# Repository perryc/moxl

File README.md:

# Mo-XL — Mower eXtra Large

An autonomous mower for large-scale grass areas like airstrips, built with ROS2 and RTK GPS.

## The Problem

Mowing a grass airstrip is a big job and the guy with the plane is often not around to cut it. This project has been kicking around for nearly 10 years now, but with "spring is coming soon" optimism, a lot of Claude Code help, and a few CDS2-ers pitching in — maybe we can cut some grass this year. The donor mower was chosen simply because we had one sitting at the farm not getting used.

The initial deployment is at CDS2 (Disley, Saskatchewan) — a 2246 ft x 78 ft grass runway that needs regular cutting. That's nearly half a mile of back-and-forth passes. RTK GPS gives centimeter-level accuracy in an open field. A robot can do this.

## The Approach

The [OpenMower](https://openmower.de/) project proved that a consumer mower can be converted to autonomous operation using ROS2, GPS, and off-the-shelf electronics. [OpenMowerNext](https://github.com/jkaflik/OpenMowerNext) by Jakub Kaflik rebuilt the software stack on modern ROS2 Jazzy with Nav2 and ros2_control.

Mo-XL takes that same architecture and scales it up — from a backyard lawn mower to a 60-inch commercial deck that can handle an airstrip. The software is forked from OpenMowerNext; the hardware is entirely custom.

## What Changed from OpenMowerNext

The fork keeps the proven ROS2 infrastructure — ros2_control, Nav2 path following, robot_localization EKF, Foxglove monitoring — and replaces everything hardware-specific:

| OpenMowerNext | Mo-XL | Why |
|---|---|---|
| VESC motor controllers | BTS7960 43A H-bridges | Different motors, 24V system |
| u-blox F9P GPS | FarmTRX RTK (CAN GPS) | We make this stuff! Let's use it |
| NTRIP client | Removed | FarmTRX handles its own RTK corrections |
| micro-ROS + custom mainboard | Mo-XL Pi HAT (custom PCB) | Single board, opto-isolated, JLCPCB assembled |
| IMU (on mainboard) | GPS magnetometer + gyro | FarmTRX sends heading (HDT/HCHDG) and rate of turn (TIROT) |
| Lawn polygon map server | Airstrip toolpath planner | Runway data from surveyed coordinates |
| Docking station | GPS park position | No charging dock — gas engine with alternator |
| YardForce 500B URDF | Custom URDF from measurements | Completely different machine |

## Hardware

### The Machine

A Swisher 60" towable rough-cut mower deck, converted from tow-behind to self-propelled:

- **Cutting deck**: Swisher 60" (1.52m), 3-blade triangle layout, B&S I/C 500cc 14.5 HP gas engine with electric start
- **Drive system**: Two electric wheelchair motors on 14.5" turf tires, chain-driven (19T→32T, 1.684:1), differential steering
- **Motor controllers**: 2x BTS7960 43A dual H-bridge boards, 24V PWM, 3.3V logic compatible
- **GPS**: FarmTRX RTK rover — NMEA0183 serial output, magnetometer heading (HDT/HCHDG), rate of turn gyro (TIROT), cm-level accuracy
- **I/O Board**: Mo-XL Pi HAT v1.0 — custom 6-layer PCB (see below)
- **Radio**: RTL-SDR v3/v4 USB dongle — monitors 122.8 MHz CTAF for aviation traffic
- **Computer**: Raspberry Pi 5 (8GB) running ROS2 Jazzy
- **Power**: 2x 12V lead-acid batteries in series (24V drive, 12V center tap for starter and Pi HAT)
- **Charging**: 24V alternator belt-driven off blade engagement belt — charges while mowing

### Key Dimensions

All dimensions from hangar measurements (Mar 2026) — see `config/hardware/moxl.yaml`.

| Measurement | Value |
|---|---|
| Rear wheel separation (center-to-center) | 1.321 m (52") |
| Rear wheel radius (turf tires) | 0.184 m (14.5" diameter) |
| Wheelbase (caster pivot to drive axle) | 1.105 m (43.5") |
| Caster separation | 1.016 m (40") |
| Cutting width | 1.52 m (60") |
| Chassis length | 1.137 m (44 3/4") |
| GPS antenna position | 0.127m fwd of drive axle, 0.80m AGL |
| Chain drive ratio | 19T motor → 32T wheel (1.684:1) |
| Total mass (estimated) | ~140 kg |

```
                 1.016m (40")
          ┌──────────────────────┐
    caster ○                      ○ caster
          │                      │
          │    1.105m wheelbase   │
          │                      │
          │      ★ GPS antenna   │
          │     (5" fwd of axle) │
          │                      │
    drive ●──────────────────────● drive
          └──────────────────────┘
                 1.321m (52")

    ●/○ = wheel    ★ = GPS antenna
    Front casters, rear drive (diff steer)
```

### Mo-XL Pi HAT v1.0

Custom Raspberry Pi 5 I/O board — single PCB replaces all direct GPIO wiring with isolated, protected I/O. 6-layer ENIG, 65 x 56.5mm Pi HAT form factor, assembled by JLCPCB.

Full spec sheet: [`hardware/moxl-hat/Mo-XL_Hat_v1.0_Spec.pdf`](hardware/moxl-hat/Mo-XL_Hat_v1.0_Spec.pdf)

| Feature | Implementation |
|---|---|
| **Power** | Hardened 12V input (TVS + EMI filter + polyfuse), XL4015 buck to 5.88V, TPS7A7001 LDO to 5.05V. Powers Pi and all HAT circuitry. |
| **2x Motor Drive** | 8 opto-isolated signals (TLP293-4) to BTS7960 modules via IDC ribbon cable. 20 kHz PWM. |
| **CAN / CAN-FD** | MCP251863T integrated controller + transceiver (SPI). TVS protected. |
| **RS-232** | MAX3221 on UART0. TX always active. |
| **SBUS** | RC receiver input via 74HC14 inverter on UART0 RX. Hardware-selectable vs RS-232 RX. |
| **4x Servo PWM** | PCA9685 16-ch PWM driver (I2C). 5.88V servo power rail. |
| **4x Analog Input** | ADS1115 16-bit ADC (I2C). On-board dividers for 12V/24V battery monitoring. |
| **K-type Thermocouple** | MAX31855 (SPI). Cylinder head temperature, 0-1024C. |
| **4x Relay Driver** | ULN2003A with flyback clamp. Engine run, start, blade engage, aux. |
| **4x Schmitt Trigger Input** | 74HC14 conditioned: engine tach + 2 wheel encoder pulses + SBUS. |
| **HAT ID EEPROM** | CAT24C256 on I2C0. Pi auto-configuration per HAT spec. |

KiCad source: [`hardware/moxl-hat/`](hardware/moxl-hat/)

### Connectors

| Connector | Type | Signals |
|---|---|---|
| J1 | JST-VH 2p | GND, +12V_RAW |
| J2 | JST-XH 4p | CANH, CANL, CAN_12V, GND |
| J3 | IDC 2x4 | Left motor (RPWM, LPWM, R_EN, L_EN, R_IS, L_IS, VCC, GND) |
| J4 | IDC 2x4 | Right motor (same as J3) |
| J5 | JST-XH 5p | RLY_RUN, RLY_START, RLY_BLADE, RLY_AUX, GND |
| J6 | JST-XH 8p | 4x servo PWM + 6V power + GND |
| J7 | JST-PH 5p | BATT_V, ALT_I, FUEL, PACK_V, GND |
| J8 | JST-PH 5p | RPM_SIG, ENC_L, ENC_R, 5V, GND |
| J9 | JST-XH 2p | TC+, TC- |
| J11 | JST-PH 3p | RS232_TX, RS232_RX, GND |
| J12 | JST-PH 3p | SBUS_IN, 5V, GND |

Unique pin counts per connector family prevent cross-plugging.

## Software Architecture

```
┌─────────────────────────────────────────────────────────────────┐
│                        moxl.launch.py                           │
├──────────┬──────────┬──────────┬──────────┬─────────────────────┤
│  URDF /  │   GPS    │  Local-  │  Nav2    │  Mission Control    │
│  ros2    │          │  ization │          │                     │
│  control │          │          │          │                     │
├──────────┼──────────┼──────────┼──────────┼─────────────────────┤
│ robot_   │ nmea_    │ heading  │ control  │ toolpath_node       │
│ state_   │ navsat_  │ _to_imu  │ _server  │ engine_controller   │
│ publisher│ driver   │ _node    │          │ blade_controller    │
│          │          │          │ planner  │ mission_node        │
│ controller         │ ekf_odom │ _server  │ safety_monitor      │
│ _manager │          │          │          │ sdr_detector        │
│          │ /gps/fix │ ekf_map  │ bt_nav   │                     │
│ diff_    │ /heading │          │          │                     │
│ drive_   │          │ navsat_  │ velocity │                     │
│ controller         │ transform│ _smoother│                     │
├──────────┴──────────┴──────────┴──────────┴─────────────────────┤
│                   twist_mux (with e-stop lock)                  │
├─────────────────────────────────────────────────────────────────┤
│                   Foxglove Bridge (web UI)                      │
└─────────────────────────────────────────────────────────────────┘
```

### ROS2 Nodes

**Localization** — GPS position and heading fused into odometry:
- `nmea_navsat_driver` — reads FarmTRX NMEA serial, publishes `/gps/fix` (NavSatFix), `/heading` (QuaternionStamped), and `/nmea_sentence` (raw NMEA for HCHDG/TIROT parsing)
- `heading_to_imu_node` — bridges GPS heading to `sensor_msgs/Imu` with speed-dependent covariance blending. Parses TIROT (rate of turn) for angular velocity and HCHDG as fallback heading source.
- `ekf_se_odom` — odom frame EKF: wheel odometry + magnetometer heading + gyro rate of turn
- `ekf_se_map` — map frame EKF: wheel odometry + GPS position + heading + gyro
- `navsat_transform_node` — converts GPS lat/lon to local map frame odometry

**Navigation** — Nav2 path following:
- `RegulatedPurePursuitController` — smooth path tracking tuned for large turning radius
- `SmacPlanner2D` — global path planning
- `VelocitySmoother` — acceleration limiting for smooth motion
- `twist_mux` — priority-based velocity command multiplexing (RC > navigation, e-stop locks all)

**Mission Control** — autonomous mowing orchestration:
- `toolpath_node` — generates headland-first mowing pattern: perimeter passes then parallel strips with step-in turns
- `engine_controller_node` — engine start/stop with CHT-driven choke logic (stub — HAT GPIO pending)
- `blade_controller_node` — blade engage/disengage via belt actuator relay (stub — HAT GPIO pending)
- `mission_node` — action server state machine: preflight (start engine, engage blades) → mow all strips via Nav2 FollowPath → return to park → shutdown. Monitors CTAF radio and evacuates when traffic is detected.
- `safety_monitor_node` — GPS fix watchdog (e-stop on RTK loss or timeout), future LiDAR obstacle detection
- `sdr_detector_node` — RTL-SDR radio traffic detector monitoring 122.8 MHz CTAF

### Custom ROS2 Interfaces

**Messages:**
- `EngineStatus.msg` — engine state (OFF/CRANKING/RUNNING/ERROR), RPM, cylinder head temp, choke
- `BladeStatus.msg` — blade state (DISENGAGED/ENGAGING/ENGAGED/DISENGAGING/ERROR)
- `MissionStatus.msg` — mission state, current strip, progress percentage
- `RadioDetection.msg` — SDR detection event: frequency, signal power, active flag, quiet duration

**Services:**
- `StartEngine.srv`, `StopEngine.srv` — engine control
- `SetBlades.srv` — blade engagement (engage/disengage)

**Actions:**
- `MowMission.action` — full autonomous mowing mission with feedback (strip progress, state)

### Toolpath Generation

The toolpath planner loads runway corner coordinates (RTK-surveyed at 0.02m accuracy), projects to UTM, and generates a headland-first mowing pattern:

1. Load runway polygon from `config/airstrips/CDS2.json`
2. Project WGS84 corners to UTM Zone 13N (EPSG:32613) via pyproj
3. Mow perimeter headland passes first (2 passes around the boundary)
4. Generate parallel strips for the interior with step-in turns
5. Densify each path with waypoints every 1.5m
6. All paths sent to Nav2 FollowPath (bypasses planner — open field needs no obstacle avoidance)

For CDS2 runway 11/29 (2246 ft x 78 ft) with a 60" deck and 5cm overlap: ~4.3 km total mowing distance.

### Aviation Radio Traffic Detector

You can't land if a mower is on the runway. Mo-XL monitors the airport traffic frequency with an RTL-SDR USB dongle (~$30) and automatically evacuates the runway when radio traffic is detected.

**How it works:**

1. `sdr_detector_node` tunes RTL-SDR to 122.8 MHz, reads IQ samples in a background thread, and computes signal power against a rolling noise floor
2. When a transmission is detected (power > noise floor + squelch threshold), the node publishes `radio_active=True` and asserts e-stop to immediately halt the mower
3. `mission_node` cancels the active FollowPath goal, navigates to the nearest pre-defined clear zone (off-runway safe area), and waits
4. After 5 minutes of radio silence, the mower resumes mowing from where it left off

**Clear zones** are defined per-runway in `CDS2.json` — three safe parking areas (north apron, midfield west, south holdshort) where the mower can wait without blocking the runway.

**Fail-open design:** If the RTL-SDR hardware isn't connected or `pyrtlsdr` isn't installed, the detector logs a warning and publishes `radio_active=False` — mowing continues unblocked. The GPS safety monitor remains the hard backstop.

## Target Airstrip

**CDS2** — Disley, Saskatchewan, Canada

| | |
|---|---|
| Runway | 11/29 |
| Dimensions | 2246 ft x 78 ft (685 m x 24 m) |
| Heading | ~117° true |
| Elevation | 1847–1861 ft |
| Magnetic declination | 7.2° East |
| UTM Zone | 13N (EPSG:32613) |

All four runway corners RTK-surveyed at 0.02m accuracy:

| Corner | Latitude | Longitude |
|---|---|---|
| NW | 50.63612190 | -105.03202723 |
| NE | 50.63603243 | -105.03175091 |
| SE | 50.63285006 | -105.03165067 |
| SW | 50.63288086 | -105.03194065 |

## Project Structure

```
moxl/
├── config/
│   ├── airstrips/CDS2.json          # RTK-surveyed runway corners
│   ├── controllers.yaml             # ros2_control diff_drive params
│   ├── gps.yaml                     # nmea_navsat_driver config
│   ├── hardware/moxl.yaml           # Physical dimensions (from hangar measurements)
│   ├── mowing_params.yaml           # Cutting width, overlap, speed
│   ├── nav2_params.yaml             # Nav2 path following tuning
│   ├── robot_localization.yaml      # Dual EKF + navsat_transform
│   └── twist_mux.yaml              # Velocity priority + e-stop lock
├── description/                     # URDF/xacro robot model
│   ├── robot.urdf.xacro            # Top-level URDF
│   ├── robot_core.xacro            # Chassis, wheels, casters, deck
│   ├── gps.xacro                   # GPS antenna link + visual
│   └── ros2_control.xacro          # BTS7960 hw_interface (mock on desktop)
├── docs/
│   ├── moxl-hat-spec.md            # Pi HAT full specification
│   └── wiring/moxl_harness.yml     # WireViz wiring harness diagram
├── hardware/moxl-hat/              # KiCad PCB design
│   ├── moxl-hat.kicad_sch          # Schematic (clean DRC)
│   ├── moxl-hat.kicad_pcb          # 6-layer PCB layout
│   ├── Mo-XL_Hat_v1.0_Spec.pdf     # Spec sheet with schematic
│   ├── pinout-table.dxf            # Bottom silk pinout (for KiCad import)
│   └── production/                 # JLCPCB fabrication files (BOM, positions, Gerbers)
├── launch/
│   ├── moxl.launch.py              # Full system launch
│   ├── gps.launch.py               # GPS driver
│   ├── localization.launch.py      # EKF + navsat_transform + heading bridge
│   ├── nav2.launch.py              # Navigation stack
│   ├── mission.launch.py           # Mission control nodes
│   ├── joystick.launch.py          # Manual teleop
│   └── sim.launch.py               # Gazebo simulation
├── src/
│   ├── msg/                         # EngineStatus, BladeStatus, MissionStatus, RadioDetection
│   ├── srv/                         # StartEngine, StopEngine, SetBlades
│   ├── action/                      # MowMission
│   ├── toolpath_planner/            # Python ROS2 package
│   │   ├── toolpath_planner/        # Core library
│   │   │   ├── coordinate_utils.py  # WGS84 ↔ UTM conversion
│   │   │   ├── polygon_loader.py    # Airport JSON → runway corners
│   │   │   └── strip_generator.py   # Headland-first pattern generation
│   │   ├── nodes/                   # ROS2 nodes
│   │   │   ├── toolpath_node.py
│   │   │   ├── heading_to_imu_node.py
│   │   │   ├── engine_controller_node.py
│   │   │   ├── blade_controller_node.py
│   │   │   ├── mission_node.py
│   │   │   ├── safety_monitor_node.py
│   │   │   └── sdr_detector_node.py
│   │   └── test/                    # 31 unit tests
│   └── lib/bts7960_hw_interface/    # C++ ros2_control plugin (TBD)
├── photos/                          # Build photos & measurements
├── HARDWARE_TODO.md                 # Hardware integration checklist
└── worlds/                          # Gazebo simulation worlds
```

## Getting Started

### Prerequisites

ROS2 Jazzy on Ubuntu 24.04 (or Raspberry Pi OS with ROS2):

```bash
sudo apt install \
  ros-jazzy-ros2-control ros-jazzy-ros2-controllers \
  ros-jazzy-diff-drive-controller ros-jazzy-robot-localization \
  ros-jazzy-nmea-navsat-driver ros-jazzy-navigation2 \
  ros-jazzy-teleop-twist-keyboard ros-jazzy-foxglove-bridge \
  ros-jazzy-xacro ros-jazzy-robot-state-publisher \
  ros-jazzy-twist-mux
```

Python dependencies:

```bash
pip install pyproj shapely numpy
```

### Build

```bash
cd ~/ros2_ws/src
git clone https://github.com/perryc/moxl.git
cd ~/ros2_ws
colcon build
source install/setup.bash
```

### Run Tests

```bash
cd src/moxl/src/toolpath_planner
python3 -m pytest test/ -v
```

All 31 tests cover coordinate conversion accuracy, strip generation geometry, and polygon loading.

### Simulation

Runs Gazebo simulation with full Nav2 navigation, toolpath planning, and mission control.

```bash
source /opt/ros/jazzy/setup.bash
cd ~/moxl && colcon build && source install/setup.bash
ros2 launch moxl sim.launch.py

# Send a mowing mission (in a second terminal)
ros2 action send_goal /moxl/mission moxl/action/MowMission \
  '{airstrip_id: CDS2, runway_id: "11/29"}' --feedback
```

> **Important:** Gazebo loads the world file from `install/`, not from `worlds/` in the source tree.
> After any change to `worlds/empty.sdf` (or a `git pull` that updates it), you must
> `colcon build` again so the updated file is copied into the install directory.

### Launch (Native ROS2)

```bash
# Full system (uses mock hardware interface on desktop)
ros2 launch moxl moxl.launch.py

# Manual teleop for testing
ros2 launch moxl joystick.launch.py
```

### Start a Mowing Mission

```bash
ros2 action send_goal /moxl/mission moxl/action/MowMission \
  "{airstrip_id: 'CDS2', runway_id: '11/29'}"
```

The mission sequences through: preflight (engine start, blade engage) → mow all strips → return to park → shutdown. Monitor progress via Foxglove at `ws://localhost:8765`.

## Status

This is an active build. The software architecture is complete; hardware integration is in progress. Pi HAT boards ordered from JLCPCB.

- [x] Fork and adapt OpenMowerNext
- [x] BTS7960 hardware interface (ros2_control plugin defined, mock for desktop)
- [x] URDF robot description (from hangar measurements, all dimensions verified)
- [x] GPS integration (nmea_navsat_driver + magnetometer heading + TIROT gyro bridge)
- [x] Toolpath planner (headland-first pattern, 31 tests passing)
- [x] Mission control (action server state machine, engine/blade stubs)
- [x] Safety monitor (GPS watchdog + e-stop)
- [x] Mo-XL Pi HAT v1.0 designed (KiCad, 6-layer, clean DRC, JLCPCB production files)
- [x] Wiring harness diagram (WireViz)
- [x] Gazebo simulation — full autonomous mowing mission completes
- [x] Aviation radio traffic detector — RTL-SDR monitors 122.8 MHz CTAF, auto-evacuates runway
- [ ] Pi HAT assembly and smoke test (boards ordered, 10 days out)
- [ ] BTS7960 GPIO driver (compile for Pi, wire motors via HAT J3/J4)
- [ ] Engine control via HAT (starter relay, choke servo, RPM tach, CHT thermocouple)
- [ ] Blade engagement via HAT (relay + belt actuator)
- [ ] Belt-driven alternator for 24V charging
- [ ] Wheel encoder pulse counters (via HAT 74HC14 inputs)
- [ ] LiDAR obstacle detection (RPLIDAR C1 ordered)
- [ ] RC manual override (SBUS via HAT)
- [ ] Field testing at CDS2

See [HARDWARE_TODO.md](HARDWARE_TODO.md) for the full hardware integration checklist.

## Acknowledgments

- [OpenMowerNext](https://github.com/jkaflik/OpenMowerNext) by Jakub Kaflik — the ROS2 foundation this project is built on
- [OpenMower](https://openmower.de/) by Clemens Elflein — the original open-source autonomous mower that proved the concept
- [Nav2](https://nav2.org/) — battle-tested robot navigation
- [robot_localization](https://docs.ros.org/en/jazzy/p/robot_localization/) — GPS + odometry fusion
- [WireViz](https://github.com/wireviz/WireViz) — wiring harness documentation
- Jack C — bled for the initial measurements so we didn't have to

## License

Apache 2.0 — see [LICENSE](LICENSE). Original OpenMowerNext code is also Apache 2.0.

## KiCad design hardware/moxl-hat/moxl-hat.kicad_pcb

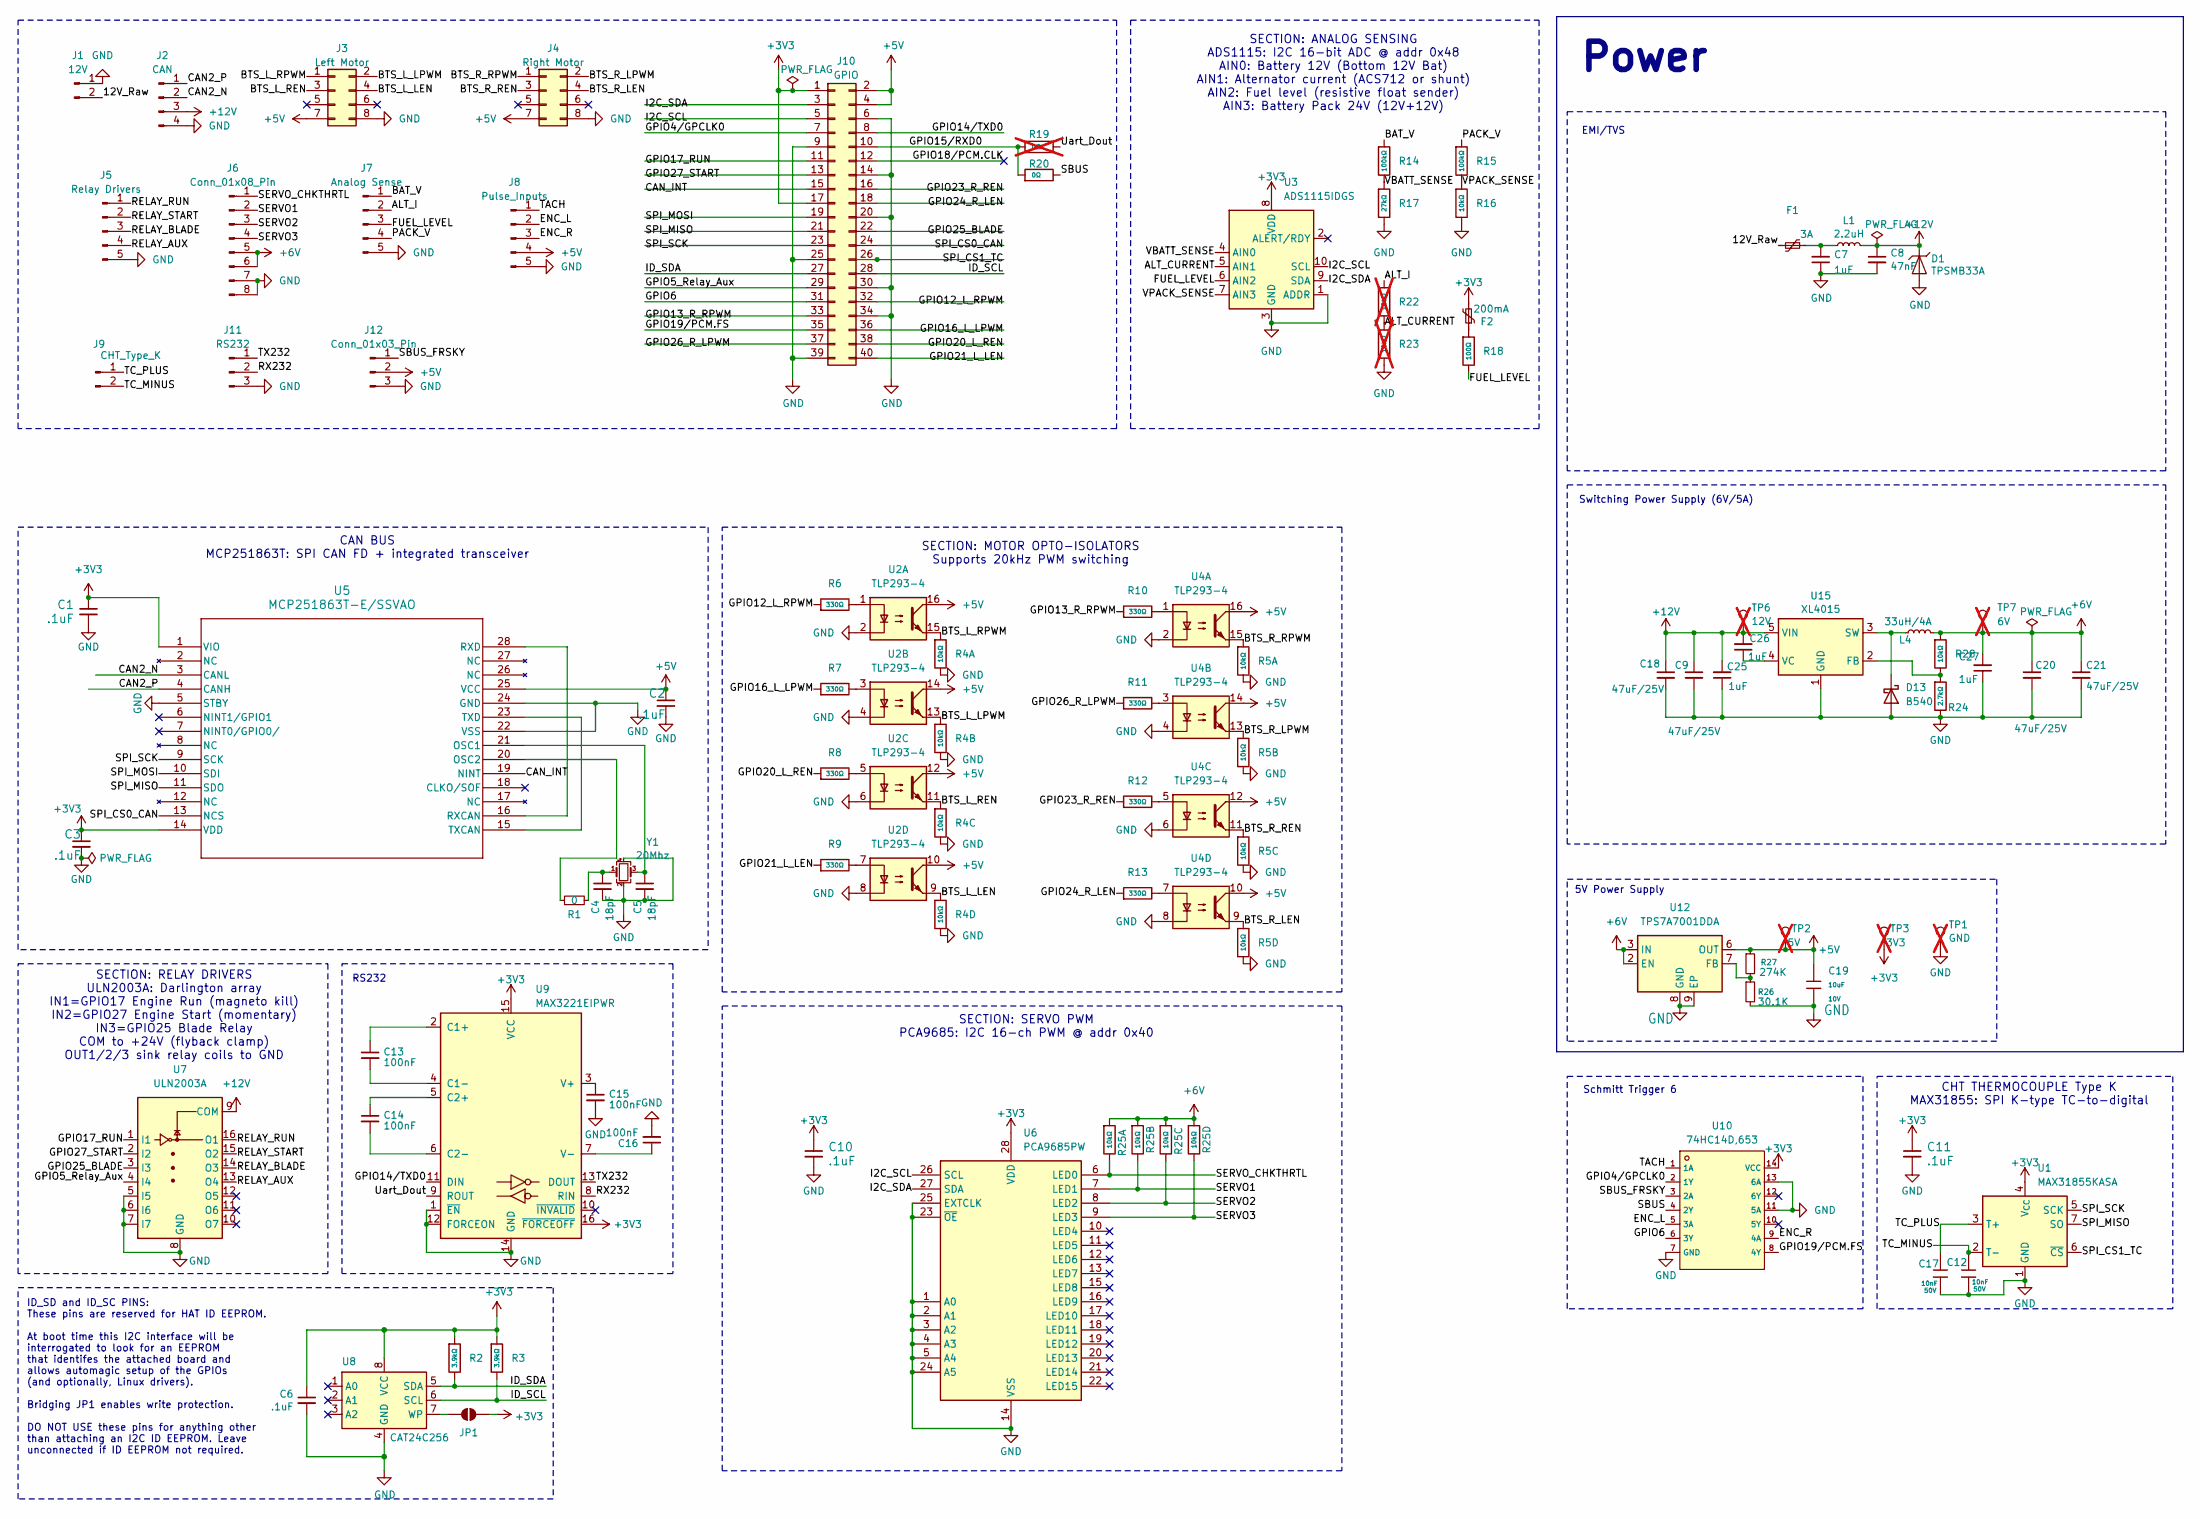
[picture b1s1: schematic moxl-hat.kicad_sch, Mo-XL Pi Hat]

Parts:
C1, C2, C3, C10, C11: .1uF; C_0603_1608Metric; Part Number CL10B104KC8NNNC; LCSC C14663
C4, C5: 18pF; C_0402_1005Metric; LCSC C1549
C6: .1uF; C_0603_1608Metric; LCSC C14663
C7, C25, C26, C27: 1uF; C_0805_2012Metric; LCSC C28323
C8: 47nF; C_0805_2012Metric; Part Number CL21B473KBCNNNC; LCSC C53134
C9, C18, C20, C21: 47uF/25V; C_1210_3225Metric; LCSC C90142
C12, C17: 10nF; C_0402; Voltage Rated 50V; Tolerance ±10%; Part CL05B103KB5NNNC; LCSC C15195
C13, C14, C15, C16: 100nF; C_0402_1005Metric; LCSC C307331
C19: 10uF; C_0603; Voltage Rated 10V; Tolerance ±10%; Part CL10A106KP8NNNC; LCSC C19702
D1: TPSMB33A; D_SMB; LCSC C726834
D13: B540; D_SMC; LCSC C72264
F1: 3A; Fuse_1812_4532Metric; LCSC C20627123
F2: 200mA; Fuse_0805_2012Metric; LCSC C20976
J1: 12V; JST_VH_B2P-VH-B_1x02_P3.96mm_Vertical; LCSC C495202
J2: CAN; JST_XH_B4B-XH-A_1x04_P2.50mm_Vertical; LCSC C594232
J3: Left Motor; PinHeader_2x04_P2.54mm_Vertical
J4: Right Motor; PinHeader_2x04_P2.54mm_Vertical
J5: Relay Drivers; JST_XH_B5B-XH-A_1x05_P2.50mm_Vertical; LCSC C157991
J6: Conn_01x08_Pin; JST_XH_B8B-XH-A_1x08_P2.50mm_Vertical; LCSC C157972
J7: Analog Sense; JST_PH_B5B-PH-K_1x05_P2.00mm_Vertical; LCSC C157993
J8: Pulse_Inputs; JST_PH_B5B-PH-K_1x05_P2.00mm_Vertical; LCSC C157993
J9: CHT_Type_K; JST_XH_B2B-XH-A_1x02_P2.50mm_Vertical; LCSC C158012
J10: GPIO; PinSocket_2x20_P2.54mm_Vertical
J11: RS232; JST_PH_B3B-PH-K_1x03_P2.00mm_Vertical; LCSC C131339
J12: Conn_01x03_Pin; JST_PH_B3B-PH-K_1x03_P2.00mm_Vertical; LCSC C131339
JP1: ID_WP; SolderJumper-2_P1.3mm_Bridged_RoundedPad1.0x1.5mm
L1: 2.2uH; L_6.3x6.3_H3; Part Number TMPC0618H-2R2MG-D; LCSC C305216
L4: 33uH/4A; L_Changjiang_FXL1040; LCSC C436575
R1: 0; R_0402_1005Metric; LCSC C17168
R2, R3: 3.9kΩ; R_0402; Overload Voltage (Max) 50V; Tolerance ±1%; Part 0402WGF3901TCE; LCSC C51721
R4, R5, R25: 10kΩ; R_0603x4; Tolerance ±5%; Part 4D03WGJ0103T5E; LCSC C29718
R6, R7, R8, R9, R10, R11, R12, R13: 330Ω; R_0603; Overload Voltage (Max) 75V; Tolerance ±1%; Part 0603WAF3300T5E; LCSC C23138
R14, R15: 100kΩ; R_0603; Overload Voltage (Max) 75V; Tolerance ±1%; Part 0603WAF1003T5E; LCSC C25803
R16, R28: 10kΩ; R_0603; Overload Voltage (Max) 75V; Tolerance ±1%; Part 0603WAF1002T5E; LCSC C25804
R17: 27kΩ; R_0603; Overload Voltage (Max) 75V; Tolerance ±1%; Part 0603WAF2702T5E; LCSC C22967
R18: 100Ω; R_0603; Overload Voltage (Max) 75V; Tolerance ±1%; Part 0603WAF1000T5E; LCSC C22775
R19: 0Ω; R_0603; Overload Voltage (Max) 75V; Tolerance ±1%; Part 0603WAF0000T5E; LCSC C21189; not fitted
R20: 0Ω; R_0603; Overload Voltage (Max) 75V; Tolerance ±1%; Part 0603WAF0000T5E; LCSC C21189
R22, R23: 10kΩ; R_0603; Overload Voltage (Max) 75V; Tolerance ±1%; Part 0603WAF1002T5E; LCSC C25804; not fitted
R24: 2.7kΩ; R_0603; Overload Voltage (Max) 75V; Tolerance ±1%; Part 0603WAF2701T5E; LCSC C13167
R26: 30.1K; R_0603; LCSC C23000
R27: 274K; R_0603; LCSC C22968
TP1: GND; TestPoint_THTPad_D1.5mm_Drill0.7mm; not fitted
TP2: 5V; TestPoint_THTPad_D1.5mm_Drill0.7mm; not fitted
TP3: 3V3; TestPoint_THTPad_D1.5mm_Drill0.7mm; not fitted
TP6: 12V; TestPoint_THTPad_D1.5mm_Drill0.7mm; not fitted
TP7: 6V; TestPoint_THTPad_D1.5mm_Drill0.7mm; not fitted
U1: MAX31855KASA; SOIC-8_3.9x4.9mm_P1.27mm; LCSC C52028
U2, U4: TLP293-4; SOIC-16_4.55x10.3mm_P1.27mm; LCSC C112623
U3: ADS1115IDGS; TSSOP-10_3x3mm_P0.5mm; LCSC C2868291
U5: MCP251863T-E/SSVAO; SSOP-28_5.3x10.2mm_P0.65mm; LCSC C5226885
U6: PCA9685PW; TSSOP-28_4.4x9.7mm_P0.65mm; LCSC C2678753
U7: ULN2003A; SOP-16_4.4x10.4mm_P1.27mm; LCSC C482013
U8: CAT24C256; TSSOP-8_4.4x3mm_P0.65mm; LCSC C79987
U9: MAX3221EIPWR; TSSOP-16_4.4x5mm_P0.65mm; LCSC C484736
U10: 74HC14D,653; SOIC-14_L8.7-W3.9-P1.27-LS6.0-BL; Supply Voltage(Single) 2V~6V; Part 74HC14D,653; LCSC C5605
U12: TPS7A7001DDA; TI_SO-PowerPAD-8; LCSC C60719
U15: XL4015; TO-263-5_TabPin3; LCSC C51661
Y1: 20Mhz; Crystal_SMD_5032-4Pin_5.0x3.2mm; Part Number TAXM20M4QLDCDT2T; LCSC C362490

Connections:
+3V3: C1.1, C3.1, C6.1, C10.1, C11.1, F2.2, J10.1, J10.17, JP1.2 (B), R2.1, R3.1, TP3.1, U1.4 (V_{CC}), U3.8 (VDD), U5.1 (VIO), U5.14 (VDD), U6.28 (VDD), U8.8 (VCC), U9.15 (VCC), U9.16 (~FORCEOFF), U10.14 (VCC)
+5V: C2.1, C19.1, J3.7, J4.7, J8.4, J10.2, J10.4, J12.2, R27.1, TP2.1, U2.10, U2.12, U2.14, U2.16, U4.10, U4.12, U4.14, U4.16, U5.25 (VCC), U12.6 (OUT)
+6V: C20.1, C21.1, C27.2, J6.5, J6.6, L4.2, R25.1, R25.2, R25.3, R25.4, R28.1, TP7.1, U12.2 (EN), U12.3 (IN)
+12V: C8.1, C9.1, C18.1, C25.2, C26.2, D1.1 (A1), J2.3, L1.2, TP6.1, U7.9 (COM), U15.5 (VIN)
/12V_Raw: F1.2, J1.2
/ALT_CURRENT: R22.2, R23.1, U3.5 (AIN1)
/ALT_I: J7.2, R22.1
/BAT_V: J7.1, R14.1
/BTS_L_LEN: J3.4, R4.4, U2.9
/BTS_L_LPWM: J3.2, R4.2, U2.13
/BTS_L_REN: J3.3, R4.3, U2.11
/BTS_L_RPWM: J3.1, R4.1, U2.15
/BTS_R_LEN: J4.4, R5.4, U4.9
/BTS_R_LPWM: J4.2, R5.2, U4.13
/BTS_R_REN: J4.3, R5.3, U4.11
/BTS_R_RPWM: J4.1, R5.1, U4.15
/CAN2_N: J2.2, U5.3 (CANL)
/CAN2_P: J2.1, U5.4 (CANH)
/CAN_INT: J10.15, U5.19 (NINT)
/ENC_L: J8.2, U10.5 (3A)
/ENC_R: J8.3, U10.9 (4A)
/FUEL_LEVEL: J7.3, R18.2, U3.6 (AIN2)
/GPIO4/GPCLK0: J10.7, U10.2 (1Y)
/GPIO5_Relay_Aux: J10.29, U7.4 (I4)
/GPIO6: J10.31, U10.6 (3Y)
/GPIO12_L_RPWM: J10.32, R6.1
/GPIO13_R_RPWM: J10.33, R10.1
/GPIO14/TXD0: J10.8, U9.11 (DIN)
/GPIO15/RXD0: J10.10, R19.1, R20.1
/GPIO16_L_LPWM: J10.36, R7.1
/GPIO17_RUN: J10.11, U7.1 (I1)
/GPIO18/PCM.CLK: J10.12
/GPIO19/PCM.FS: J10.35, U10.8 (4Y)
/GPIO20_L_REN: J10.38, R8.1
/GPIO21_L_LEN: J10.40, R9.1
/GPIO23_R_REN: J10.16, R12.1
/GPIO24_R_LEN: J10.18, R13.1
/GPIO25_BLADE: J10.22, U7.3 (I3)
/GPIO26_R_LPWM: J10.37, R11.1
/GPIO27_START: J10.13, U7.2 (I2)
/I2C_SCL: J10.5, U3.10 (SCL), U6.26 (SCL)
/I2C_SDA: J10.3, U3.9 (SDA), U6.27 (SDA)
/ID_SCL: J10.28, R3.2, U8.6 (SCL)
/ID_SDA: J10.27, R2.2, U8.5 (SDA)
/PACK_V: J7.4, R15.1
/RELAY_AUX: J5.4, U7.13 (O4)
/RELAY_BLADE: J5.3, U7.14 (O3)
/RELAY_RUN: J5.1, U7.16 (O1)
/RELAY_START: J5.2, U7.15 (O2)
/RX232: J11.2, U9.8 (RIN)
/SBUS: R20.2, U10.4 (2Y)
/SBUS_FRSKY: J12.1, U10.3 (2A)
/SERVO1: J6.2, R25.7, U6.7 (LED1)
/SERVO2: J6.3, R25.6, U6.8 (LED2)
/SERVO3: J6.4, R25.5, U6.9 (LED3)
/SERVO_CHKTHRTL: J6.1, R25.8, U6.6 (LED0)
/SPI_CS0_CAN: J10.24, U5.13 (NCS)
/SPI_CS1_TC: J10.26, U1.6 (~CS)
/SPI_MISO: J10.21, U1.7 (SO), U5.11 (SDO)
/SPI_MOSI: J10.19, U5.10 (SDI)
/SPI_SCK: J10.23, U1.5 (SCK), U5.9 (SCK)
/TACH: J8.1, U10.1 (1A)
/TC_MINUS: C12.1, J9.2, U1.2 (T-)
/TC_PLUS: C17.1, J9.1, U1.3 (T+)
/TX232: J11.1, U9.13 (DOUT)
/Uart_Dout: R19.2, U9.9 (ROUT)
/VBATT_SENSE: R14.2, R17.1, U3.4 (AIN0)
/VPACK_SENSE: R15.2, R16.1, U3.7 (AIN3)
GND: C1.2, C2.2, C3.2, C4.2, C5.2, C6.2, C7.1, C8.2, C9.2, C10.2, C11.2, C12.2, C15.2, C16.2, C17.2, C18.2, C19.2, C20.2, C21.2, C25.1, C27.1, D1.2 (A2), D13.2 (A), J1.1, J2.4, J3.8, J4.8, J5.5, J6.7, J6.8, J7.5, J8.5, J10.6, J10.9, J10.14, J10.20, J10.25, J10.30, J10.34, J10.39, J11.3, J12.3, R4.5, R4.6, R4.7, R4.8, R5.5, R5.6, R5.7, R5.8, R16.2, R17.2, R23.2, R24.2, R26.2, TP1.1, U1.1 (GND), U2.2, U2.4, U2.6, U2.8, U3.1 (ADDR), U3.3 (GND), U4.2, U4.4, U4.6, U4.8, U5.5 (STBY), U5.22 (VSS), U5.24 (GND), U6.1 (A0), U6.2 (A1), U6.3 (A2), U6.4 (A3), U6.5 (A4), U6.14 (VSS), U6.23 (~OE), U6.24 (A5), U6.25 (EXTCLK), U7.5 (I5), U7.6 (I6), U7.7 (I7), U7.8 (GND), U8.4 (GND), U9.1 (~EN), U9.12 (FORCEON), U9.14 (GND), U10.7 (GND), U10.11 (5A), U10.13 (6A), U12.8 (GND), U12.9 (EP), U15.1 (GND), Y1.2, Y1.4
unnamed: C4.1, R1.2, Y1.1
unnamed: C7.2, F1.1, L1.1
unnamed: D13.1 (K), L4.1, U15.3 (SW)
unnamed: F2.1, R18.1
unnamed: JP1.1 (A), U8.7 (WP)
unnamed: R6.2, U2.1
unnamed: R7.2, U2.3
unnamed: R8.2, U2.5
unnamed: R9.2, U2.7
unnamed: R10.2, U4.1
unnamed: R11.2, U4.3
unnamed: R12.2, U4.5
unnamed: R13.2, U4.7
unnamed: C5.1, U5.21 (OSC1), Y1.3
unnamed: R1.1, U5.20 (OSC2)
unnamed: U5.16 (RXCAN), U5.28 (RXD)
unnamed: U5.15 (TXCAN), U5.23 (TXD)
unnamed: C13.1, U9.2 (C1+)
unnamed: C13.2, U9.4 (C1-)
unnamed: C14.1, U9.5 (C2+)
unnamed: C14.2, U9.6 (C2-)
unnamed: C15.1, U9.3 (V+)
unnamed: C16.1, U9.7 (V-)
unnamed: R26.1, R27.2, U12.7 (FB)
unnamed: R24.1, R28.2, U15.2 (FB)
unnamed: C26.1, U15.4 (VC)

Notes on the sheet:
CHT THERMOCOUPLE Type K MAX31855: SPI K-type TC-to-digital
EMI/TVS
RS232
CAN BUS MCP251863T: SPI CAN FD + integrated transceiver
SECTION: ANALOG SENSING ADS1115: I2C 16-bit ADC @ addr 0x48 AIN0: Battery 12V (Bottom 12V Bat) AIN1: Alternator current (ACS712 or shunt) AIN2: Fuel level (resistive float sender) AIN3: Battery Pack 24V (12V+12V)
5V Power Supply
ID_SD and ID_SC PINS: These pins are reserved for HAT ID EEPROM. At boot time this I2C interface will be interrogated to look for an EEPROM that identifes the attached board and allows automagic setup of the GPIOs (and optionally, Linux drivers). Bridging JP1 enables write protection. DO NOT USE th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
SECTION: SERVO PWM PCA9685: I2C 16-ch PWM @ addr 0x40
Switching Power Supply (6V/5A)
Schmitt Trigger 6
SECTION: RELAY DRIVERS ULN2003A: Darlington array IN1=GPIO17 Engine Run (magneto kill) IN2=GPIO27 Engine Start (momentary) IN3=GPIO25 Blade Relay COM to +24V (flyback clamp) OUT1/2/3 sink relay coils to GND
SECTION: MOTOR OPTO-ISOLATORS Supports 20kHz PWM switching
Power

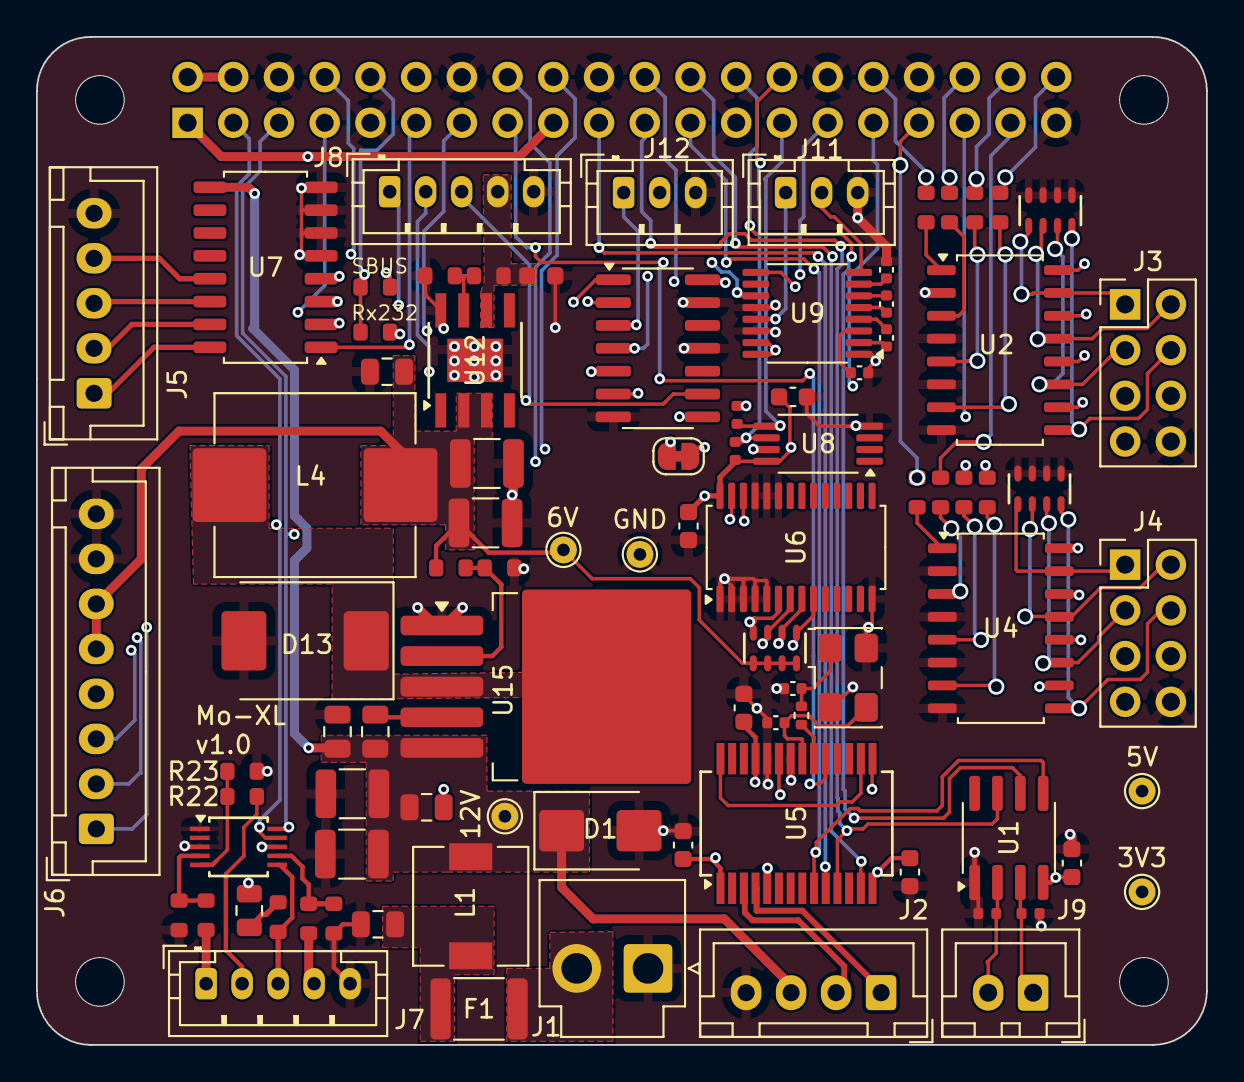
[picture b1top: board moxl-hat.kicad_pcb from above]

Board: 6 copper layers, 65.0 x 56.0 mm, 92 parts (1 on the bottom side), 94 nets.

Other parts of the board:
MH1, MH2, MH3, MH4: MountingHole_2.7mm_M2.5

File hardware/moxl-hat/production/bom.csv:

Designator,Footprint,Quantity,Value,LCSC Part #
"C1, C10, C11, C2, C3, C6",0603,6,.1uF,C14663
"C12, C17",C_0402,2,10nF,C15195
"C13, C14, C15, C16",0402,4,100nF,C307331
"C18, C20, C21, C9",1210,4,47uF/25V,C90142
C19,C_0603,1,10uF,C19702
"C25, C26, C27, C7",0805,4,1uF,C28323
"C4, C5",0402,2,18pF,C1549
C8,0805,1,47nF,C53134
D1,D_SMB,1,TPSMB33A,C726834
D13,D_SMC,1,B540,C72264
F1,1812,1,3A,C20627123
F2,0805,1,200mA,C20976
J1,JST_VH_B2P-VH-B_1x02_P3.96mm_Vertical,1,12V,C495202
J10,PinSocket_2x20_P2.54mm_Vertical,1,GPIO,
J11,JST_PH_B3B-PH-K_1x03_P2.00mm_Vertical,1,RS232,C131339
J12,JST_PH_B3B-PH-K_1x03_P2.00mm_Vertical,1,Conn_01x03_Pin,C131339
J2,JST_XH_B4B-XH-A_1x04_P2.50mm_Vertical,1,CAN,C594232
J3,PinHeader_2x04_P2.54mm_Vertical,1,Left Motor,
J4,PinHeader_2x04_P2.54mm_Vertical,1,Right Motor,
J5,JST_XH_B5B-XH-A_1x05_P2.50mm_Vertical,1,Relay Drivers,C157991
J6,JST_XH_B8B-XH-A_1x08_P2.50mm_Vertical,1,Conn_01x08_Pin,C157972
J7,JST_PH_B5B-PH-K_1x05_P2.00mm_Vertical,1,Analog Sense,C157993
J8,JST_PH_B5B-PH-K_1x05_P2.00mm_Vertical,1,Pulse_Inputs,C157993
J9,JST_XH_B2B-XH-A_1x02_P2.50mm_Vertical,1,CHT_Type_K,C158012
JP1,SolderJumper-2_P1.3mm_Bridged_RoundedPad1.0x1.5mm,1,ID_WP,
L1,L_6.3x6.3_H3,1,2.2uH,C305216
L4,L_Changjiang_FXL1040,1,33uH/4A,C436575
R1,0402,1,0,C17168
"R10, R11, R12, R13, R6, R7, R8, R9",R_0603,8,330Ω,C23138
"R14, R15",R_0603,2,100kΩ,C25803
"R16, R28",R_0603,2,10kΩ,C25804
R17,R_0603,1,27kΩ,C22967
R18,R_0603,1,100Ω,C22775
"R2, R3",R_0402,2,3.9kΩ,C51721
R20,R_0603,1,0Ω,C21189
R24,R_0603,1,2.7kΩ,C13167
"R25, R4, R5",R_0603x4,3,10kΩ,C29718
R26,R_0603,1,30.1K,C23000
R27,R_0603,1,274K,C22968
U1,SOIC-8_3.9x4.9mm_P1.27mm,1,MAX31855KASA,C52028
U10,SOIC-14_L8.7-W3.9-P1.27-LS6.0-BL,1,"74HC14D,653",C5605
U12,TI_SO-PowerPAD-8,1,TPS7A7001DDA,C60719
U15,TO-263-5_TabPin3,1,XL4015,C51661
"U2, U4",SOIC-16_4.55x10.3mm_P1.27mm,2,TLP293-4,C112623
U3,TSSOP-10_3x3mm_P0.5mm,1,ADS1115IDGS,C2868291
U5,SSOP-28_5.3x10.2mm_P0.65mm,1,MCP251863T-E/SSVAO,C5226885
U6,TSSOP-28_4.4x9.7mm_P0.65mm,1,PCA9685PW,C2678753
U7,SOP-16_4.4x10.4mm_P1.27mm,1,ULN2003A,C482013
U8,TSSOP-8_4.4x3mm_P0.65mm,1,CAT24C256,C79987 
U9,TSSOP-16_4.4x5mm_P0.65mm,1,MAX3221EIPWR,C484736
Y1,Crystal_SMD_5032-4Pin_5.0x3.2mm,1,20Mhz,C362490

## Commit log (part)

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2026-03-02 Clarify monitoring system for runway traffic detection
    Updated the description of the Aviation Radio Traffic Detector to clarify the monitoring system.
2026-03-02 Revise explanations for GPS and IMU in README
    Updated the reasoning for using FarmTRX RTK and clarified the IMU functionality with the FarmTRX GPS.
2026-03-09 Update GPS entry from NMEA to CAN in README
